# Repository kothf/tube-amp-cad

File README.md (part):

# Tube Amp CAD

Design and simulate vacuum-tube amplifiers in the browser. You draw a
schematic, and a circuit simulator computes the operating points and
waveforms. A curve tracer, an oscilloscope, a spectrum analyzer and a Bode plotter show
the result as bench instruments would.

**Live:** [kothf.github.io/tube-amp-cad](https://kothf.github.io/tube-amp-cad/) ·
also on [aerocat.tech/tools](https://aerocat.tech/tools/)

There's nothing to install, no account and no server. Everything runs on
your machine, and the browser saves your circuit.

**Browsers:** tested in Chrome, Edge and other Chromium browsers (Brave,
Vivaldi, Opera) and in Safari (the whole test suite also runs in WebKit).
Firefox is not tested.

## Contents

- [The schematic editor](#the-schematic-editor)
- [Parts](#parts)
- [Measuring on the schematic](#measuring-on-the-schematic)
- [Drawings, documents and exports](#drawings-documents-and-exports)
- [Instruments](#instruments)
- [Board Design](#board-design)
- [Keyboard shortcuts](#keyboard-shortcuts)
- [How the simulator works](#how-the-simulator-works)
- [Accuracy](#accuracy)
- [Run it locally](#run-it-locally) · [Development](#development) · [Contributing](#contributing)

## The schematic editor

- **Placing parts.** Pick a part in the palette on the left and click the
  sheet; Shift-click places several. The search box at the top of the palette
  finds:
  - parts by name;
  - part numbers: 2N3904, IRF540, 1N4742A, 125ESE, 373BX …;
  - tubes: EL84, 6N2P, 300B …;
  - values: `47k` offers a 47 kΩ resistor or potentiometer, `100n` a
    100 nF capacitor, `47u` an electrolytic, `5H` a choke, `300V` a supply.

  ↓ / ↑ walk the results and Enter picks the marked one (or the first). Each
  row shows a small picture of the part's own symbol; pointing at a part shows
  it large in the preview card under the list, with what it is. Drag a part
  onto the sheet to place it there. Right-click a part (or ☆ in the preview)
  to keep it in Favorites; Recent lists the last parts picked. Click a group's
  title to fold it; the browser remembers which groups are open.
- **Wiring.** Click a pin, click the corners, and finish on a pin or a wire.
  <kbd>W</kbd> starts a wire anywhere. A wire ending on another wire joins it
  with a junction dot; plain crossings stay unconnected.
- **Editing.**
  - Drag parts and their wires follow; drag a wire segment sideways to move
    it.
  - <kbd>Space</kbd> rotates (also while placing or dragging a part; <kbd>R</kbd>
    works too), <kbd>M</kbd> mirrors left to right, <kbd>D</kbd>
    duplicates, <kbd>Del</kbd> deletes, with undo and redo.
  - Mirror works for every part that can rotate, including any part added to
    the library later. So a complementary pair, or a tube taking its grid from
    the right, can be drawn without crossing wires. The oscilloscope mirrors
    too, so its inputs can come in from the right; its screen stays upright.
- **Inspector (right).** Every value of the selected part: resistance
  ("4.7k"), tube type, transformer model and tap, generator level in Vpk, Vrms
  or dBV. With a simulation result it adds:
  - the part's operating point: Va, Vg, Ia, Pa and gain for a tube; Vce, Ic,
    hFE and dissipation for a transistor;
  - checks against the part's ratings.

  With nothing selected it shows a power summary instead: output into the
  speakers, and tube, transistor and resistor dissipation.
- **Live or on demand.** The circuit re-simulates after every edit, or turn
  *Live* off and press *▶ Simulate* (<kbd>Ctrl</kbd>+<kbd>Enter</kbd>).
  - Either way, slow power supplies are run until they have fully settled.
  - The button shows the run's progress ("■ Stop · 48 %"); press it again to
    stop a long run.
  - When a steady-state run and the oscilloscope's power-on transient run at
    once, the status line shows both on one line with one progress bar.
- **Checks.** Unconnected pins, shorted parts, a missing ground, sheet
  connectors without a partner, and parts beyond their ratings: resistor
  power, output-transformer DC current, transistor Vce and dissipation, zener
  power, and for tubes:
  - anode dissipation (Pa) and screen dissipation (Pg2), averaged over the
    signal cycle; screen voltage; cathode current;
  - heater-to-cathode voltage at its worst instant, against the rating for
    that direction (a rectifier's or a raised cathode's "heater negative"
    rating is often higher). The heater is taken as grounded; set *Heater DC
    potential* on the tube for an elevated heater supply;
  - the grid circuit resistance (grid stopper, grid leak, volume pot) against
    the largest the tube allows with cathode or with fixed bias, where too
    much lets the tube run away as it warms;
  - a rectifier's rectified current and peak inverse voltage.

  The tube's inspector shows each of them as a share of its rating. Ratings
  come from Katsnelson & Larionov for the Soviet tubes and from the makers'
  datasheets for the others (RCA, Philips, Mullard, Western Electric); a
  rating a datasheet does not give is not checked.
- **Window tabs at the bottom.** Like the part / assembly / drawing tabs of a mechanical CAD, a strip under the status bar switches between the schematic, the board, the open instruments and the manual inside one browser tab. Schematic and Board are always there; an instrument or the manual gets a tab when opened (or from **+**). × closes a tab, ⧉ moves it to a window of its own for a second monitor (the tab stays dimmed and brings that window up), and a reload keeps the tabs. *View ▾ → Windows as tabs* (on by default) turns them off: every tool in a window of its own, as before.
- **Toolbar.** One row: the *Schematic | Board* switch (the same switch in the Board window leads back; Alt+B and Alt+S from any window; the board is a tab at the bottom of the CAD window), *File ▾*, *View ▾* (the Voltages, Currents and Legend on the schematic (the legend fades while the pointer is over it, so the drawing under it shows), the bill of materials and Checks tabs under it, ticked on or off, Windows as tabs and the interface language), *Edit ▾* (undo, redo, rotate, mirror, duplicate, delete, copy, paste, select all, reusable blocks, renumber), undo / redo, the *Select | Wire | Probe* tool, zoom and *Fit* (wheel zoom and panning stay smooth on big circuits with the stickers and the animation on: the picture is stretched while the wheel turns and drawn sharp when it stops, and only what is on screen is drawn), *● Live | ▶ Simulate | ∿ Animate*, *Analyze ▾* next to Simulate (the instruments: oscilloscope, spectrum analyzer, Bode plotter and curve tracer, each in a tab at the bottom; the analyses: tolerance runs, power sweep, listen, parameter sweep and noise and hum, each a tab under the schematic), and **?**, the Help menu (quick help and shortcuts, F1; the manual; about). The menus follow other simulators: instruments and analyses sit with simulation (Multisim's and LTspice's Simulate menu), the board is reached by its switch (KiCad's Switch to PCB editor, Proteus's tabs) and the manual is under Help, so there is no Windows menu. *RU / EN* switches the interface between Russian and English (also *View ▾ → Interface*): the CAD, the Board window, the instruments and the hover hints follow, every open window at once, and so does the manual (`help-ru.html`, its Russian translation). The right mouse button on a part or wire opens the editing commands there. At 900 px and below the inspector is a drawer that slides in when something is selected (*Inspector* button).
- **Hints and manual.** Every field, readout, instrument setting and model coefficient explains itself when you rest the pointer on it (labels with a dotted underline). The manual, `help.html` (in Russian `help-ru.html`, chosen by the interface language; the *RU / EN* button at the top of its contents switches it), opens from **?** → *Manual* (the Help menu), the help dialog, or **?** in each instrument. It covers:
  - a quick start, then every part and field;
  - all 99 tubes in a sortable table;
  - every readout and the checks;
  - the instruments and the board layout;
  - a design cookbook, and the simulator's equations and limits.

  It is searchable.
- **AI assistant** (AI ▾ and the AI tab under the schematic), with your own
  key for Claude, ChatGPT or Gemini, kept in the browser and sent only to
  that provider:
  - ask about the circuit or the app; the model sees the parts, nets,
    simulated voltages, operating points and Checks, and the manual;
  - *Design from a description*: the model designs the circuit, the CAD
    draws and simulates it and sends the Checks back for revisions;
  - *Tube from a datasheet*: a PDF read into ratings, pinout and a Koren
    model fitted to its plate curves, reviewed before it joins the library;
  - *Explain my circuit*, stage by stage;
  - *Fix the checks*: value changes checked against the parts, applied with
    one click, re-simulated and compared.
- **Auto-tune** (the Tune tab, no key needed): set goals such as "10 W at
  ≤ 1 % THD" and the values that may change; an optimizer tries values, the
  simulator judges each, and the best are rounded to E24/E12. *AI start*
  lets the model pick the values and ranges. With no goals yet, one button
  adds the usual pair: the speaker's power a quarter above what it gives now,
  at ≤ 1 % THD.
- **Layout.**
  - Drag the edge of the palette, the inspector or the BOM to resize it, and
    double-click the edge to reset it. The same goes for the side panels of
    the instrument windows.
  - <kbd>F1</kbd> or the **?** button opens the help with every shortcut and a link to the manual.
  - Shortcuts go by the key's position, so they work with a Russian or any
    other keyboard layout.
- **Reusable blocks** (Edit ▾ → Blocks…): select a stage or a whole
  channel and make it a block, then place it as many times as needed (the
  two channels of a stereo amplifier). A value changed on any copy changes
  on every copy; after changing the drawing of one copy, *Update block from
  selection* redraws the others. Sheet-connector names stay each copy's
  own, designators are numbered per copy, and blocks can be kept in a
  library in the browser for other circuits.
- **Files.**
  - File → Open / Save / Save as (JSON). In Chrome and Edge, Save writes back
    to the opened file after asking; in Safari and other browsers it
    downloads the file.
  - The circuit is also autosaved in the browser, and File → Autosaves…
    keeps a copy every 5 minutes of editing and when the tab closes (the
    newest 60, in this browser only); Open puts one back on the sheet.
  - File → Recent files lists the last 8 circuits opened or saved (and the
    examples opened), newest first; a click opens one again. Chrome and Edge
    read the file itself again; when it is gone, not allowed, or the browser
    cannot open files by itself, the copy kept in the browser at the last open
    or save opens instead (the status line says so). *Clear recent files*
    empties the list.
  - File → Revisions… keeps a project's history as numbered revisions (r1,
    r2…) with a message, what changed, pictures of the sheet and the board,
    milestones, Compare on the sheet and Restore. *Kept in* chooses where: on
    aerocat.tech (the site's owner only, `server/share/`), or in a **vault**,
    a folder on your computer that you choose (`cad-vault.js`; Chrome and
    Edge read and write it, Safari and Firefox open it read only). A vault holds plain files: a folder for each project with
    `project.json`, and each revision as `r<n>.json` (File → Open reads it)
    with its pictures and release files. Add as many vault folders as you
    like, one for each project for example, and switch between them in
    *Kept in*; nothing leaves the computer. The project manager
    (`projects.html`) lists either store and copies a project with all its
    revisions between the folder and the site.
  - File → Share link… packs the whole design (circuit, imported tubes,
    board) into a link; whoever opens it gets the same circuit. On
    aerocat.tech the link is short (`/s/<id>`, kept by the link store in
    `server/share/`); elsewhere the design rides after `#` in the address.
  - Icons: the tools, Fit and Inspector, and every item of the File, View,
    Edit, AI and Windows menus (in Board Design the Route, Board, Export and
    View menus too) carry a line icon from the app's own set (`icons.js`,
    drawn in the text colour, nothing loaded from elsewhere). The names stay
    next to them; a narrower window shows the toolbar buttons by their icon
    alone, the tooltip naming each, so the toolbar keeps one row.
  - The open file's name shows in the toolbar and the browser tab's title; a
    yellow • marks unsaved changes (the board's too). A circuit not saved to
    a file yet (a new one, or an example) shows its title block's title (or
    its identification number) in grey italics, such as "NE555 metronome:
    astable into a speaker"; "Untitled" only when the title block is empty.

## Parts

| Group | Parts |
|---|---|
| Passive | resistor (with power rating, marked in the symbol per ГОСТ 2.728), potentiometer (lin/log), capacitor, electrolytic, choke with DCR, speaker: an ideal resistor, or a **loudspeaker** from its Thiele–Small parameters (Re, Le, fs, Qms, Qes; typical guitar and hi-fi drivers to start from) with its impedance and phase curve in the inspector; **protection**: fuse (5 × 20, 6.3 × 32, TR5; Checks from 75 % of its rating), inrush limiter NTC (Ametherm SL series, simulated at its self-heated resistance), varistor (TDK SIOV); capacitors take a voltage rating that Checks watches; **headphone loads** 32, 250, 300 and 600 Ω with their resonance peaks; **potentiometer** tapers lin / log / reverse log, sections R1.1 + R1.2 as one dual-gang (stereo) pot, an optional on–off switch (switched pot) |
| Switches & relays | changeover switch, on–off toggle, push buttons (normally open / closed), rotary selector (2–12 ways), all ganged by section names; **relays** Omron G5LE-1 (SPDT) and G5V-2 (DPDT) with 5 / 12 / 24 V coils (coil resistance and inductance, must-operate and release, timing checked against ngspice); **vactrols** VTL5C3 and VTL5C1 (the cell following the LED's current, with the datasheet's turn-on and turn-off times) |
| Transformers | generic single-ended and push-pull/UL output transformers with a **Model** list of Hammond and Edcor parts (the part remembers its model and shows it, marked *(edited)* when you type your own values over it), a saturating core and a **Core material** whose hysteresis loop gives the bass distortion and core loss of a real transformer (silicon steel, nickel or amorphous), and a generic power transformer; **interstage and input transformers** (turns ratio, optional centre-tapped secondary, primary and leakage inductance, winding capacitance, DCRs, the DC the core is gapped for; typical interstage, microphone, moving-coil and line presets), checked against ngspice's coupled inductors; the seven **Hammond 125SE** output transformers and 25 **Hammond 300-series** power transformers, modelled from the maker's drawings (winding resistances, inductance, excitation, no-load voltages, ratings) |
| Tubes | every tube's anode temperature from its dissipation, glowing red when over-driven (red-plating); **110 tubes**: the Soviet receiving tubes from Katsnelson & Larionov, «Отечественные приёмно-усилительные лампы и их зарубежные аналоги» (1981), including triodes and double triodes (6С2С, 6С33С, 6Н1П…6Н33Б), voltage and output pentodes (6Ж1П, 6Ж32П, 6П1П, 6П3С, 6П14П, 6П27С…), triode-pentodes as two sections (6Ф1П, 6Ф3П, 6Ф4П, 6Ф5П) and kenotrons (5Ц3С, 5Ц4С, 6Ц4П…), with the handbook's ratings and pinouts; plus Western tubes from their makers' datasheets (12AX7, 12BH7A, 6CG7, EL84, 6AQ5A, ECL82, EL34, KT66, KT88, 6AS7G, 300B, 211, 845, GZ34, 5Y3GT, EZ81, 6X4…). Pentodes can be used triode-connected. **Import SPICE model…** adds any tube model of your own (see below).; **mercury-vapour rectifiers** 83 (full-wave) and 866A (half-wave): a constant 15 V arc drop, glowing blue under Animate; heaters glow and warm up from switch-on under Animate |
| Semiconductors | **diodes**: standard rectifiers 1N4001/1N4004/1N4007, 1N5404/1N5408, fast and ultrafast UF4007, UF5408, MUR160, MUR460, HER108, FR107, Schottky BAT85, 1N5817, 1N5819, 1N5822, SB1100, SiC Schottky C3D02060A, C3D04060A, C4D02120A, the 1N4148, with reverse recovery; **bridge rectifiers** DF04M, DF10M, W04G, W10G, B250C2300-1500A, GBU4J, GBU8K, KBU8K, KBPC2510, KBPC3510; zener diodes, the 1 W 1N4728A … 1N4764A series and 5 W 1N5349B … 1N5388B (3.3–200 V); LEDs (red, yellow, green, blue) for cathode bias; **NPN** 2N2222A, 2N3904, BC107, BC547B, BD139, MPSA42, MJE340 and **PNP** 2N2907A, 2N3906, BC177, BC557B, BD140, MPSA92, MJE350; **drivers and power output** in complementary pairs: 2SD669A/2SB649A, 2SC4793/2SA1837, MJE15032/MJE15033, TIP41C/TIP42C, 2SC5200/2SA1943, MJL3281A/MJL1302A, MJL21194/MJL21193, and in TO-3 (on wires, for a chassis heatsink) MJ15003/MJ15004, MJ15024/MJ15025, 2N3055/MJ2955; **germanium** (VBE about 0.2 V, low fT): USSR MP39B, MP40A, MP41A, MP42B, MP25B, MP26B, MP38A (NPN), GT402G/GT404G, P213B (МП39Б … П213Б) and Western AC127/AC128, AC187/AC188, OC71, NKT275, 2N404, AD149, AD161/AD162, with their collector leakage (ICBO, doubling every 10 °C); every bipolar transistor has a **Temperature** (VBE −2 mV/°C, hFE and leakage rising) and **Cooling**: self-heating in free air or on one of four shared heatsinks, the junction at the temperature its own dissipation gives (class-AB bias drift, thermal runaway, a VBE multiplier tracking its outputs on the heatsink); a SPICE part's transistors follow its Temperature by their own XTI, EG, XTB and TNOM, and a lone transistor model can heat itself too; **N-MOSFETs** 2N7000, BS170, IRF510, IRF540, IRF820, IRF840, IRFP240, IRFP250, IRFP460, the laterals 2SK1058 and ECX10N20, and the depletion DN2540 and LND150 for current sources; **P-MOSFETs** BS250, IRF9540, IRF9610, IRF9640, IRFP9240 and the laterals 2SJ162 and ECX10P20. The power models are fitted to the datasheets (hFE and its fall at high current, VBE, capacitances; for MOSFETs the typical transfer curve); the drivers and power parts (and BD139/BD140) also have base and emitter resistance fitted to the datasheet's typical VBE curve, so their VBE rises with the current as on the bench; **JFETs** (SPICE JFET, checked against ngspice): N-channel J201, J113, J310, 2N5457, MPF102, 2SK170, LSK170B, 2SK30A, P-channel J175, 2N5460, 2SJ74 |
| Sources | DC supplies: DC supply (positive for B+, negative for grid bias, with an internal resistance), power rail (the one-pin VCC arrow: an ideal supply to ground, joined by name), current source (constant current with an output resistance). AC sources: signal generator (sine, square, triangle; Vpk, Vrms or dBV; and for the Transient tab pulse, piecewise linear, exponential and FM, with SPICE's PULSE, PWL, EXP and SFFM parameters), AC mains (feeds a power transformer). Instruments and records: **guitar pickup** (EMF behind the coil's R and L, its capacitance and the cable; single-coil, P-90 and humbucker presets) and **phono cartridge** (moving magnet or moving coil, playing a tone cut with the RIAA curve, or flat). Controlled sources: voltage-controlled voltage (SPICE E) and current (SPICE G) sources, for behavioural models (a G with ra in parallel is a tube's small-signal model); **batteries**: 9 V PP3, AA cells and packs, Li-ion 18650 and packs, 12 V lead-acid, with the charge left and the internal resistance |
| Gas-discharge tubes | **voltage regulators** 0A2, 0B2 (miniature), 0A3, 0C3, 0D3 (octal): dark until the striking voltage, then the maintaining voltage plus the regulation over the current range, out below the extinction current (so 0.1 µF across one makes a relaxation oscillator); Checks for not striking and the current range; **neon lamps** NE-2, NE-2H, ИН-3 (strike, maintain, either polarity; flashers); **magic eyes** 6E5, 6Е5С, 6U5 (triode fitted to RCA's data, the shadow from the ray-control voltage). Under Animate the neons glow orange, the regulators violet and the eyes open and close; **magic eyes** EM84 / 6Е3П (bars) and 6Е1П (noval fan) from their datasheets; **incandescent lamps** #47, #44, #1869, #327, 60 W 230 V (tungsten resistance by current, glowing on the sheet); **nixie** ИН-14 (the lit digit glows) |
| Ground & connectors | Ground, sheet connector; **jacks** (6.35 mm mono switched, mono, stereo, 3.5 mm stereo, RCA), **IEC C14 inlet**, **terminal blocks** (2–8 ways, 5.08 / 7.5 mm), **pin headers** (2.54 mm), **Faston tabs** (6.3 / 4.8 mm), **XT power connectors** (Amass XT30 / XT60 / XT90, male and female, right-angle or vertical PCB, solder cups, on a lead, XT90-S anti-spark; Amass order codes in the BOM; detailed 3D / STEP bodies with shroud, pins and sockets), with the makers' footprints |
| Integrated circuits | **op-amps**: TL071, TL072 (dual), TL074 (quad) with JFET inputs, LM741, LM301A (compensated by your own capacitor between pins 1 and 8), LM324 (quad, single supply, inputs and output down to V−) and the audio types NE5532 (dual, low noise), OPA134 / OPA2134 (FET input) and LM4562 (55 MHz); each with its datasheet's open-loop gain, gain-bandwidth, slew rate, output swing, short-circuit current, input bias and supply current. The amplifiers of a dual or quad (DA1.1 … DA1.4) share one DIP-8 or DIP-14 on the board; **NE555 timer** (DIP-8 on the board): the 5k–5k–5k divider, both comparators, the latch, reset, the output (VCC − 1.4 V high, 8 Ω low, about 120–250 mA at most) and discharge stages and the chip's supply current, from TI's data. Its latch switches at the instant a comparator crosses, not on the time grid, so the timing does not depend on the step; the inspector reads the output's frequency and duty cycle; **voltage regulators**: LM317, LM317L, LM338, LM337 (adjustable) and 7805, 7809, 7812, 7815, 7824, 78L05, 78L12, 7905, 7912, 7915 (fixed), with the reference, error amplifier, current limit, dropout, line regulation (ripple rejection) and an LM317's minimum load; **TL431** shunt reference; **power amplifiers** LM386 (internal gain network, 20–200), TDA2050 and LM3886 (with its mute current), their output power at clipping as the datasheets |
| Instruments | two-channel oscilloscope (its screen live on the schematic, full window on double-click), with the spectrum analyzer and the Bode plotter reading its channels; **panel meters**: moving-coil ammeter or voltmeter and a VU meter, the needle on the sheet with a meter's ballistics under Animate |
| Document | IEC 61082 drawing frame with title block, text note |

### Your own tube models (SPICE import)

*Import SPICE model…* in a tube's inspector adds a tube from any SPICE model:
Norman Koren's, Ayumi's, Duncan's, Derk Reefman's or a maker's library.
Paste the `.SUBCKT … .ENDS` text or open the file.

- **It runs as written.** Behavioural sources (`B`, `E`/`G VALUE={…}`, linear
  `E`/`G`) and their expressions are evaluated directly, with `.PARAM`,
  `.FUNC`, `PARAMS:`, continuation lines, unit suffixes and the usual
  functions (`exp`, `ln`, `pwr`, `pwrs`, `uramp`, `limit`, `if`, `atan`, `tanh`
  …). Internal nodes are solved too, such as the grid-current resistor and
  diode of Koren's models. Capacitors are left out, since the simulator's
  tubes have none.
- **Pins:** read from the model's comment (`; P G K`, `A G2 G1 K` …). Without
  a comment, the assignment that behaves like a tube is chosen. You can always
  change it, and the curves show at once whether it is right.
- **What it's like:** each imported tube takes its socket, pinout and heater
  from a tube you choose, so the board footprint and the warnings work. Pa
  and Va maximums are set in the dialog.
- **Parts already placed:** a placed part keeps its own copy. When its
  library part has changed, the library dialog (*Update them*) and the
  part's inspector (*Update from the library*) bring it up to date; values,
  part numbers and wires stay, one Undo takes it back.
- **Where it's kept:** in the browser, and inside every circuit file that
  uses it, so the file opens on another computer. The curve tracer shows it
  with its model, and the SPICE netlist export writes the subcircuit as
  imported.
- **Checked:** Koren's published 12AX7 model gives the same currents as the
  built-in Koren equations with the same parameters.

### Any part from a maker's SPICE model (the SPICE part)

A part the library does not have (another op-amp, a regulator, a power
MOSFET, a transistor, a diode) runs on the model its maker publishes. Place
*SPICE part* (Integrated circuits), press *Model…* in its inspector and paste
the model or open the file.

- **One simulator.** The model is turned into the simulator's own elements,
  so the part runs with the valves in everything the program does: live
  simulation, steady state, tolerance runs, Tune, the instruments.
- **What it reads:** `.SUBCKT … .ENDS` (nested subcircuits, `PARAMS:`,
  `.PARAM`, `.FUNC`) or a lone `.MODEL`; R, C, L, coupled inductors (`K`), DC
  sources, diodes (series resistance, breakdown), bipolar transistors
  (Gummel-Poon with leakage terms and terminal resistances), MOSFETs (levels
  1, 2 and 3 each by its own equations with the bulk as a fourth pin, bulk
  junctions and Meyer's gate capacitances; LTspice's `VDMOS`), JFETs, controlled sources
  `E G F H` (linear, `VALUE={…}`, `TABLE`, `POLY`), behavioural `B` sources
  with `V()` and `I()`, switches `S` and `W`; PSpice, LTspice and ngspice
  spellings.
- **Symbol and pins:** a lone transistor or diode model takes that device's
  symbol; five pins are offered as an op-amp in the usual order; anything
  else is a box with the model's pins. Each pin of the model is set to a pin
  of the symbol, to ground or to nothing.
- **Transfer functions:** `LAPLACE` sources (PSpice's and LTspice's
  spellings), any ratio of polynomials in s, run exactly; `FREQ` tables
  fitted by a ratio of polynomials (vector fitting).
- **Transmission lines:** lossless `T` lines (`Z0=` with `TD=`, or `F=` and
  `NL=`, or PSpice's `L`, `C` and `LEN`), delayed exactly in the waveform and
  as e^(−jωTD) in the frequency response.
- **What it refuses, with the reason:** `LAPLACE` other than a ratio of
  polynomials, a `FREQ` table's `DELAY`, `CHEBYSHEV` filters,
  lossy transmission lines, digital (`A`) devices, BSIM MOSFETs, expressions of
  time. Junction capacitances follow the voltage across them and step their
  charge; a transistor's transit times (TF, TR) shape the waveform and the
  frequency response; a VDMOS power MOSFET's gate-drain capacitance follows
  CGDMIN … CGDMAX with its drain voltage (the Miller plateau).
- **Where it's kept:** inside the circuit file. The SPICE export writes the
  part as one line with its model as it came; the board gives it a DIP-8 /
  SOIC-8, a transistor or diode case, or a DIP in the model's pin order.
- **Checked:** a bench of device models, sources, a switch, a table and a
  polynomial gives ngspice's operating point within 0.1 %
  and its frequency response to 10 MHz within 0.02 dB
  (`tests/spicenet.test.mjs`), and `npm run test:ngspice` runs 64 makers'
  op-amp models against ngspice (`tests/models.mjs`): the output voltage
  within 2 %, gain and phase from 10 Hz to 1 MHz within 0.1 dB and 1° up to
  20 kHz, 0.3 dB and 3° up to 1 MHz.

### Pin rules (ERC)

Every pin has a role (an input, an output, a supply pin, a source, a plain
terminal) and the Checks hold the wiring to it (`cad-erc.js`):

- an input with **no DC path**: a grid behind its coupling capacitor without
  a leak, a gate, a base or an op-amp input with nothing but capacitors on
  it (the path is followed through resistors, chokes, windings, switches);
- an IC's **supply pin fed by nothing**, or both supply pins on one net;
- **outputs wired together**, to ground or straight to a supply;
- a supply shorted by its own wiring.

A SPICE part takes the roles of its symbol. All 20 examples pass.

### Your own parts library

*My library* at the top of the parts panel holds your own parts: each is data,
not code, a drawing with pins, a footprint and, if you give it one, a SPICE
model. *Parts library…* in the panel opens it.

- **Add part… by part number:** type the maker's part number (TL072CP, 2N3904,
  IRF540N), choose the package, place it. The SPICE model is looked up in the
  public [KiCad-Spice-Library](https://github.com/kicad-spice-library/KiCad-Spice-Library)
  (an index of about 49,000 names ships with the app, `spice-index.json`; the
  one model's file is downloaded when you add the part). The drawing follows
  from what the model is; a dual or quad op-amp becomes a library part with a
  unit per amplifier. A number the app has built in (2N3904, TL072, LM317T,
  NE555P) is offered as the built-in part first. No model for the number: the dialog says so and takes
  the maker's file from you instead.

- **From KiCad's libraries:** *Add from KiCad files…* reads symbol libraries
  (`.kicad_sym`) and footprints (`.kicad_mod`), several at once. A symbol
  library lists its symbols with a Find box; tick the ones to add. Derived
  symbols (`extends`) come with their parent's drawing.
- **Drawn here:** *New part…* and *Edit drawing…* open the symbol editor:
  Line, Rectangle, Circle, Text and Pin tools, Select to move and delete,
  Undo, units of a package, a table of the pins, and *Make a box from a list
  of pins* (one line per pin, as on a DIP or with sides) for ICs. Pins snap
  to the sheet's grid; a pin number used twice is refused.
- **Footprint:** a part takes the footprint its symbol names or its KiCad
  filters allow as soon as that footprint is in the library; the list shows
  the ones with a pad for every pin first. A pin goes to the pad of its
  number.
- **Footprint drawn here:** *Draw…* and *Edit…* beside the Footprint list open
  the footprint editor, in millimetres: *Make a usual package* (DIP, a row,
  SOIC, QFP or two pads from the count, pitch, row distance, pad and hole),
  Pad, Hole, Line, Rectangle and Circle tools, a grid from 2.54 to 0.1 mm,
  typed coordinates, a table of the pads, Undo, zoom. A pin left without a
  pad is named; every part that uses the footprint follows an edit.
- **SPICE model:** *Model…* sets a maker's `.SUBCKT` or `.MODEL` on the
  part's own pins; the part is then simulated as written (see the SPICE part
  above). Without a model it is left out of the simulation.
- **Units:** a dual op-amp's amplifiers and supply pins are placed unit by
  unit (the inspector's *Unit of the package*) and share one footprint under
  one designator (DA1.1, DA1.2, DA1.3). They are simulated: a model of one
  amplifier set on unit A goes on every unit drawn like it, with the supply
  pins of the package shared; a model of the whole package is used once.
- **Where it's kept:** in this browser (IndexedDB), and as a file
  (`my-parts.tubelib`) with *Save as a file* / *Open a library file…*. A part
  on the sheet carries its drawing, footprint and model in the circuit file,
  so the circuit opens anywhere.
- **Code:** `part-lib.js` (data, no DOM), `cad-symedit.js` (the symbol
  editor), `cad-fpedit.js` (the footprint editor), `cad-library.js` (the dialog and
  the store), `LIB.part` in `cad-components.js`, `KicadImport.readSymbols` /
  `readFootprint`; tests in `tests/partlib.test.mjs` and
  `tests/e2e/08c-parts-library.mjs`.

### Examples

**File ▾ → Gallery…** opens circuits drawn from published sources and compared
with them (see [Accuracy](#accuracy)), and five transistor power amplifiers of
the app's own (7 to 12 transistors each) on SMD boards. The **start screen** (shown when the CAD
opens on an empty sheet, and from *File ▾ → Gallery…*) has *New circuit*,
*Open file* and every example as a picture of its first sheet, by kind; untick
*Show this when the CAD opens* to start straight on the sheet. The pictures are
drawn by `node scripts/example-thumbs.mjs` (run it after changing an example).

The example schematics are drawn to be read: signal from left to right,
supplies at the top and the bottom, one ground bar with a single ground symbol
per area instead of a symbol at every part, each supply rail as one bus with a
single rail symbol, the transistor amplifiers' supply terminal with its
decoupling capacitors in one block, square corners, and no wire through a part
or a label.

Every example also carries a finished two-layer board, laid out the way a
board designer would place it rather than by the automatic placer: signal
flowing from the input jack across to the output transformer leads, the input
kept away from the output and the supply, grid parts and grid leaks at their
socket pins, cathode parts under their valve, anode loads beside it, heaters
hand-routed as a pair (one wire on each layer, side by side) along an edge or a
corridor between the valves, B+ along the edge, hot resistors kept 10 mm or more
from electrolytics, power devices on the heatsink edge, panel parts (jacks, pots,
terminals) on the board edges, M3 screw holes in the corners and within 40 mm
of every valve socket, and a ground pour on the bottom. The grid router routed
the rest; every board opens with 0 connections open and 0 rule messages:

| Example | Parts | Source |
|---|---|---|
| Gubin three-tube amplifier | tubes | Igor Gubin, radionic.ru: stereo single-ended 6N23P-EV + 2 × 6P14P, no coupling capacitors, pentode / triode switch |
| Gubin stereo amplifier with 5Ц4С supply | tubes | GUB-245-01 (Radio 4/1957; musicangel.ru Fig. 3), three sheets: 373BX transformer, 5Ц4С, capacitor input and 2.5 H choke; two 6N23P-EV + 6P14P channels; with a routed two-layer board (no rule violations) |
| Single-ended 2A3, Hammond 1627SEA | tubes | RCA 2A3 data (250 V, −45 V, 60 mA, 2.5 kΩ, 3.5 W): 6SN7 driver, cathode bias; 3.6 W at 1.8 % THD |
| Push-pull EL84 ultralinear, Hammond 1608 | tubes | Mullard-style: 12AX7 stage, split-load phase splitter, 2 × EL84 UL into 8 kΩ, 14 dB feedback; 11 W at 0.9 % THD, the core saturating at 15 Hz |
| Push-pull 6V6 guitar amplifier, Hammond 1750H | tubes | Tweed-style: 12AX7 stage, split-load splitter, cathode-biased 6V6GT pair, no feedback; 7.7 W at 2 % THD |
| 12AX7: plate resistor vs current source | tube + transistor | J. Broskie, TubeCAD (2000): gain 70 with a 150k plate resistor, 100 with an MPSA92 current source |
| 12AX7 stage + IRF820 follower | tube + MOSFET | The GE 12AX7 data sheet's resistance-coupled stage (gain 50) driving a MOSFET follower, which feeds an 8 Ω speaker through a parafeed output transformer (about 0.5 W) |
| 10 W complementary MOSFET amplifier | MOSFETs | homemade-circuits.com, fig. 1 |
| 2N3904 common emitter, RE unbypassed | transistor | University of Washington lab notes (2017), bench measurements |
| 2N3904 common emitter, RE bypassed | transistor | the same, with 10 µF across RE |
| 12 W amplifier, complementary feedback pairs (SMD) | transistor | this app's own design: ±15 V, current-source input and VAS, CFP outputs in D²PAK; 12 W at 1 % THD; all-SMD board |
| 50 W amplifier, MJL4281A / MJL4302A outputs | transistor | this app's own design: ±30 V, LED-referenced current sinks, CFP outputs in TO-264 on the board edge; 51 W at 1 % THD |
| 14 W class-A amplifier, current-sink output | transistor | this app's own design: ±18 V single-ended class A, 4 × TIP36C, 1.8 A sink; 14 W at 1 % THD |
| 30 W quasi-complementary amplifier (SMD) | transistor | this app's own design: ±25 V, current mirror, bootstrapped VAS, TIP41C outputs in D²PAK; 32 W at 1 % THD; all-SMD board |
| 40 W amplifier, complementary MOSFET output (SMD) | MOSFETs | this app's own design: ±30 V, IRF540N / IRF9540N in D²PAK; 38 W at 1 % THD; all-SMD board |
| NE555 astable multivibrator | 555 | 555-timer-circuits.com: 1k / 10k / 100 nF, 678 Hz at 51.8 % (formula 686 Hz, 52.4 %) |
| NE555 flashing LED | 555 | 555-timer-circuits.com: 1K / 470K / 1 µF, 1.51 Hz (formula 1.53 Hz) |
| NE555 metronome | 555 | 555-timer-circuits.com: 250K speed pot at 50k, 22 µF, speaker; 0.641 Hz (formula 0.648 Hz) |
| NE555 car tachometer | 555 | 555-timer-circuits.com: one-shot 47k / 100 nF, 5.16 ms pulses (1.1 RC = 5.17 ms); meter current proportional to the spark rate |
| NE555 simplest oscillator | 555 | 555-timer-circuits.com: output to capacitor through 10k, 100 nF: 572 Hz at 60 % (a full-swing output would give 721 Hz at 50 %) |

An example opens unsaved (the toolbar shows its title), so *Save* asks for a
file name. Ctrl+Z brings back
the circuit that was on the sheet.

## Measuring on the schematic

- **Voltage and current on every wire.**
  - Each net carries a sticker with its DC voltage, and each run of wire one
    with its DC current and direction ("↓1.38mA"). In a mains-fed circuit
    both are averaged over the settled window, as a meter reads them.
  - **∿ Animate** plays one signal cycle slowed to 3 s: dots run along each
    wire with its DC or its AC current (from the simulation's terminal
    currents at 120 instants, capacitors' C·dV/dt included), chosen by the
    node's voltage. Where the node's DC voltage is at least its AC rms, violet
    dots flow steadily with the DC current; elsewhere pale dots swing with
    the AC current. Each node's wires turn
    orange as it swings up and blue as it swings down. Tube heaters glow
    once simulated and, from the moment Animate is pressed, warm up from
    cold over each tube's own warm-up time.
  - **Play it live under Animate**: drag a pot's wiper (or turn it with the
    wheel) and click a switch, button, selector or switched jack; the
    circuit is simulated again as you turn, and letting go is one undo step.
  - AC is marked apart from DC: a net with AC on it adds it in cyan as
    "~20.1Vrms" after the yellow DC ("162V ~20.1Vrms"); a net with no DC
    shows the AC alone. Wires carrying the signal (AC at least 1 % of the DC)
    glow cyan, so the signal path stands out from supply and bias nets.
  - Currents come from every part's terminal currents and are passed along
    the wiring, so a junction shows how the current splits. On the 12AX7
    above, 1.02 mA from the plate resistor splits into 1 mA anode and 15 µA
    into the scope probe.
  - The stickers are placed where they cover no text, no symbol and no other
    sticker. If there is no room at all, a sticker is left out.
  - Hovering a wire shows its voltage, AC swing and current in the status
    bar. *View ▾ → Voltages / Currents* turns the stickers on and off.
- **Voltmeter probe.** The *Probe* tool (<kbd>P</kbd>, beside Select and
  Wire) reads a node like a bench meter. Point at any wire or pin after a
  simulation: a card beside the pointer shows the DC voltage, AC rms,
  peak-to-peak and frequency, with a small scope trace of the waveform
  (DC coupled, triggered, auto-ranging), and the node's wires glow yellow.
  - A click leaves the probe on that node. Its card stays on the sheet and
    keeps reading through edits and new simulations, also after you go back
    to Select: handy with *Live* on while you turn a value in the inspector.
  - <kbd>Esc</kbd>, the card's × or a click on empty sheet removes it.
- **Scope screens on the schematic.** An oscilloscope part shows its two
  channels live; double-click it for the full instrument.
- **Power-on transient.** The oscilloscope can show the first seconds after
  switch-on: capacitors start empty and every source switches on at t = 0.
  In every scenario but *Hot restart* the tubes' cathodes start cold as well and heat with
  their own time constant, from the heater's power and the kind of cathode
  (directly heated 1–2 s, standard indirectly heated 5–8 s, heavy power tubes
  8–12 s, slow-start rectifiers such as the GZ34 10–15 s; or the tube's own
  *Warm-up time constant*), emitting by Richardson's law. The run then
  shows B+ overshooting on cold tubes, draws the capacitors' voltage ratings
  as dashed lines, and warns of a capacitor over its rating, a rectifier
  overdrawn while its cathode is still cold (cathode stripping) and a
  switch-on surge. *Auto* duration covers the slowest warm-up (5–60 s).
  A report strip under the screen lists these events in time order, tagged
  Critical, Warning or Info (B+ settling to ±1 % among them); click one to zoom
  there. Time presets (keys 1–4: Inrush, Warm-up, Settled, Whole) and a log
  time axis show the millisecond inrush and the seconds of warm-up alike.
  Warm-up lanes show each tube's emission rising ("warm at" 90 %, orange
  where it was overdrawn cold); any capacitor can be plotted from the run
  without a probe, and B+ is plotted by itself when no probe is wired.
  *Scenario*: cold start, hot restart, a standby switch (B+ after the
  heaters) or a soft start (a resistor or the NTC shorted by a relay). The
  trace draws as the run goes, with the time left; *Stop* keeps the record.

## Drawings, documents and exports

- **IEC drawings.**
  - Symbols follow IEC 60617.
  - Designations use the classic letter codes (R1, C1, L1, T1, VL1.1, VD1,
    VT1, HL1, SA1, BA1, G1, P1, as in ГОСТ 2.710), with automatic
    renumbering in reading order.
  - Tube pin numbers sit beside each terminal; the section follows the
    designation (VL1.1 / VL1.2).
  - Labels are placed per IEC 61082-1: left of vertical symbols, above
    horizontal ones.
- **Sheets.**
  - *File → New* starts a sheet with an ISO 5457 frame, a reference grid and
    an ISO 7200 title block (A4 to A1, landscape or portrait). *File → Add
    sheet* adds further sheets. A title block value too long for its cell
    wraps onto two or three lines instead of running into the next cell.
  - Sheet connectors with the same signal name join their wires across
    sheets and show where their partners are, grouped by row: "A3,5 B2,5,8"
    (on several sheets "1/A3,5 2/C1,4"). A name used five times or more (B+,
    a bias line) reads as a supply rail and shows no list; hovering any
    connector shows all its partners' zones in the status bar.
  - Frames are locked against accidental moves; unlock one in its inspector.
  - A circuit with several sheets opens on sheet 1. The Sheet list, or <kbd>F</kbd>
    pressed twice, shows them all.
  - A scroll bar under the drawing marks every sheet: drag it to scroll, click a
    sheet's mark to show it, or step between sheets with its arrows (Page Up /
    Page Down).
- **PDF and PNG.**
  - *Print…* (Ctrl+P) prints the sheet in view, all sheets or the bill of
    materials through the browser's print dialog; in the Board window it prints
    the copper layers at 1:1, the toner-transfer pages, the assembly drawing or
    the drill map.
  - *Save as PDF* writes every sheet as a vector page.
  - *Export sheet…* saves the sheet in use, each sheet as its own file, or
    all sheets in one PDF.
  - PNG at 150, 300 or 600 dpi, black on white like the PDF or in the
    editor's colours.
- **Bill of materials.** *View ▾ → Bill of materials* (<kbd>B</kbd>) opens the parts list
  under the schematic (its other tab, *Checks*, lists every wiring problem and part beyond its rating):
  - equal parts on one line with designator ranges (R1-R4); both sections of
    a dual tube count once; a tube-socket line per base;
  - ratings (resistor wattage, transistor Vceo / Ic / Ptot / package,
    transformer ratings), and for each capacitor the first standard voltage
    rating at or above 1.25 × the peak voltage the simulation puts across it
    (a series string of 450 V parts above 550 V for an electrolytic);
  - a part made SMD on the board names its package ("Resistor, SMD 1206"),
    on a line apart from the through-hole parts of the same value;
  - the simulated worst case: dissipation, capacitor peak voltage, LED
    current;
  - a part number you can type in, saved with the circuit. A maker's number
    fills the *Package* column. *Look up* asks DigiKey's parts database
    (with your own free DigiKey API key, kept in your browser) for the
    package, case size, height and lead spacing; a few things are read from
    the number itself with nothing fetched (a size written in it, a leaded
    resistor series' body and leads, a chip size, a film capacitor's spacing,
    a semiconductor's package from its order code). Amber where it disagrees
    with the schematic. Board Design
    takes the footprint it names, and the silkscreen and 3D body follow the
    real size (or a size set by hand in the board inspector).

  Click a line to select its parts; selecting a part scrolls to its line.
  Export as TXT, CSV, XLSX or PDF.
- **Tolerance runs.** *Analyze ▾ → Tolerance runs* opens the *Tolerance* tab
  under the schematic. It simulates the circuit as drawn and then once per run
  with every resistor, pot and capacitor at a random value within its
  tolerance (±5 % and ±20 % by default) and every tube drawing more or less
  current than its model (±20 %). The table shows each value's nominal, min,
  mean, max and spread over the runs, and how many runs took a part over its
  rating:
  - each tube's Ia, Va and Pa, each transistor's current and dissipation,
    each speaker's output and each scope channel's AC;
  - values are normally distributed with the tolerance as 2σ, cut off at the
    tolerance; a seed repeats the same runs;
  - the runs share every processor core. On a circuit slow to settle (a
    valve-rectified supply, say) each varied run starts from the circuit as
    drawn already settled, so it has only a short way to go: the stereo
    Gubin example's 10 runs take 5.4 s instead of 11 s on 4 cores, with the
    same table.
- **Power sweep.** *Analyze ▾ → Power sweep* opens the *Power* tab under the
  schematic. It simulates the circuit at a row of input levels (from −24 to
  +12 dB of the generator's level by default; every generator is scaled
  together, the mains is not) and reads the output power at 1 %, 5 % and
  10 % THD:
  - the output is a speaker's power or a scope channel's AC;
  - a chart of THD and the 2nd and 3rd harmonics against the output, and a
    table of every level, with *Use* to set the generator to it;
  - around the THD marks the sweep adds levels where the distortion jumps
    between two of them, so a clipping output stage is read closely. The
    stereo Gubin example reads 1.71 W at 1 % THD in 12 s on 4 cores.
- **Listen.** *Analyze ▾ → Listen* opens the *Listen* tab under the schematic: a
  recording played through the simulated circuit, heard through the
  computer's speakers, with A/B between input and output as it plays:
  - a guitar riff made here, the generator's own tone, or your WAV or MP3 file
    (a stereo file drives two generators, two speakers play in stereo);
  - the level in dB from the generator's amplitude, to push the circuit into
    clipping and hear it;
  - rendered at 48 kHz, every sample a simulation step, a piece of the clip per
    core (each with a 0.4 s lead-in from the settled circuit, joined with a
    crossfade, on whole mains periods); *Save WAV* keeps the output.
- **Parameter sweep.** *Analyze ▾ → Parameter sweep* opens the *Sweep* tab under
  the schematic: one value of one part (a resistor, a capacitor, a pot's
  wiper, a supply's voltage, a generator's frequency…) stepped over a range,
  log or linear, the circuit simulated at every step on all cores:
  - a table of every tube's Ia, Va and Pa, transistor current and
    dissipation, speaker power and THD, scope channel AC and THD, each with a
    trend line, its range and the steps over its rating;
  - click a line to plot it against the value; a scope channel also overlays
    its wave at every step; click a step to set the part to it;
  - it starts on a resistor and plots the speaker's power (or the first scope
    channel), so *Run* gives a useful curve straight away.
- **Transient.** *Analyze ▾ → Transient* opens the *Transient* tab under the
  schematic: the circuit run in time from its own start to its own stop, the
  general-purpose time simulation (SPICE's `.tran`):
  - *Stop* and *Max step* (blank = Stop/500), *From* (when the record
    starts), a start from the operating point or from zero (SPICE's `uic`),
    and initial conditions (`.ic`) as `out=4 C3.1=0`;
  - the steps are adaptive (the error of each step is estimated from the
    last three; linear capacitors and inductors are integrated by the
    trapezoid rule, the rest by Gear), and the corners of every source's
    waveform are hit exactly;
  - traces by net name, connector, scope channel (`P1 CH1`) or part pin
    (`R3.2`); the chart draws min/max per pixel, a cursor reads every trace,
    drag to zoom, double-click to show all; min, max, p-p, average, RMS and
    end value per trace, and *CSV* writes them all;
  - a waveform viewer: any part's current (`I(R3)` into its first pin,
    `I(Q1.C)`) and expressions over the run (`V(OUT,IN)`,
    `V(R1.1,R1.2)*I(R1)` in W, `d()`, `integ()`, `db`, `abs`, `min`/`max`…,
    with units that follow the arithmetic, `wave-math.js`); several panes,
    each with its own scale, in time or as a spectrum (*FFT*, Hann window,
    the strongest line named); cursors A and B (click, Shift+click) with Δt,
    1/Δt and each trace's values, the figures taken between them; *Keep as
    reference* draws a run dashed under the next ones;
  - **DC sweep** (the tab's first list; SPICE's `.dc`): the operating point at
    2 to 1001 values of a part's value (a supply's voltage, a current source,
    a resistor, a pot…) or of the temperature of every transistor (by its own
    XTI, EG, XTB, as SPICE), each point continuing from the one before; the
    same viewer with the swept value on the axis. Checked against ngspice's
    `.dc` on six circuits (diode, zener knee, BJT output curve, BJT bias
    against temperature, MOSFET transfer curve, current-fed diode) within
    0.5 % of the swing, `tests/dcsweep-ngspice.mjs`;
  - **Measurements** (SPICE's `.meas`): *+ Measure…* adds max, min, p-p,
    average, RMS, integral, value and slope at a point, first crossing of a
    level, rise and fall time (10–90 %), overshoot, settling time (2 %),
    period, frequency and duty cycle of a trace, over the span shown or from
    cursor A to B;
  - the signal generator's *pulse*, *PWL*, *exponential* and *FM* waves and
    the `PULSE`/`SIN`/`EXP`/`SFFM`/`PWL` sources and `time` in B sources of a
    SPICE part play here (the other analyses take their DC value).
  - Checked against ngspice's `.tran` on ten benches (RC, RLC ring,
    rectifier, PWL into RL, EXP, SFFM, current pulse, B source reading time,
    a BJT switch, `uic` with `.ic`): within 1 % of each node's swing (2 % for
    the ring and the switch), `tests/transient-ngspice.mjs`; and four
    switching converters (buck 12→5 V, boost 5→12 V, flyback 24→5 V with
    coupled windings, class-D half bridge): start-up within 2 % of the swing,
    output average within 1 % and ripple within 10 %, `tests/smps-ngspice.mjs`.
- **KiCad.** *Export KiCad project* (File menu) writes a ZIP for KiCad 7 or
  later: the schematic (each symbol as drawn here, dual valves as units of
  one symbol, a sheet per drawing frame), the board when its parts are
  placed, the net classes, custom rules for the clearance by voltage, and
  the symbol and footprint libraries. Pins carry their pads' numbers, so
  *Update PCB from Schematic* pairs the two. Checked with KiCad 7.0.11: on
  every example KiCad's netlist of the schematic joins exactly the pads the
  board joins, and its DRC agrees with the Board window's.
- **Open KiCad project.** *File ▾ → Open KiCad project…* opens a KiCad
  schematic and its board as a circuit here: select the project's
  `.kicad_sch` sheets, its `.kicad_pcb` and `.kicad_pro` together, or a ZIP
  of the folder (KiCad 6 and later; a schematic or a board alone opens too).
  - Symbols the program has a part for become that part and simulate:
    passives, diodes, transistors (by their pin names), op-amps, the 555,
    connectors, and valves under any of their names (ECC83 = 12AX7 = 6Н2П).
    Everything else is kept as KiCad draws it, an *Imported part*: wired on
    the sheet and the board, in the BOM, left out of the simulation.
  - Nets are KiCad's: junctions, local, global and hierarchical labels,
    power symbols, hierarchical sheets (a sheet each), buses by name. On 13
    of KiCad's 14 demo projects the nets equal KiCad's own netlist pin for
    pin (`tests/kicad-oracle.mjs`, with kicad-cli); the one that differs
    has wires drawn on top of each other, which the list points out.
  - The board comes with its outline, footprints as the file has them,
    tracks, vias, pours, keep-outs, holes and texts (top and bottom copper);
    its rules are set from the layout.
  - A project this program exported comes back as it was. A list says what
    came over and what to check.
- **Noise and hum.** *Analyze ▾ → Noise and hum* opens the *Noise* tab under
  the schematic: what the amplifier puts out with no signal:
  - thermal, tube (2.5/gm, pentode partition, 1/f), shot and FET channel
    noise carried to the output; flat and A-weighted over 20 Hz – 20 kHz,
    the input noise, a density chart and each part's share;
  - the supply's ripple at the output (every harmonic of the mains, from the
    steady state with the generators quiet, named after its mains source,
    e.g. "From G1 (230 V 50 Hz mains)") and an estimate of AC heater hum
    (one side grounded, centre-tapped or DC);
  - the signal-to-noise ratio in dB(A), noise and hum together, re 1 W.
- **SPICE.** *Export SPICE netlist* writes an LTspice netlist: tubes as
  behavioural sources with the same equations the simulator uses, transistors
  as Q and M elements with their `.model` lines.

## Instruments

| Curve tracer | Oscilloscope |
|---|---|
|  |  |

- **Curve tracer.** Select a tube or a transistor in the schematic to see its
  curves (transistors: IC–VCE, IC–VBE and hFE–IC, or ID–VDS, ID–VGS and gm–ID,
  from the simulator's own BJT, MOSFET and JFET models, germanium too) with:
  - the operating point;
  - the curve at the circuit's bias;
  - the simulated load line: the last whole cycle of the signal, an ellipse
    when the load is reactive, with arrows for the direction;
  - Pa max and 70 % Pa (a transistor's Ptot and its voltage and current ratings);
  - dissipation, swing, gain and THD at the plate.

  It also has the tube library with socket pinouts, the Koren parameters, an
  LTspice `.subckt` export, and a fitter for your own measured curves.
- **Oscilloscope.**
  - Two channels, DC or AC coupled, with 10× (10 MΩ) or 1× (1 MΩ) probes
    that load the circuit like real ones.
  - Auto volts/div with offset; the timebase locks to the measured frequency;
    edge trigger; X-Y mode.
  - Scale labels on every axis: time below, CH1's volts on the left, CH2's on
    the right. They sit on round values and follow zoom and position.
  - Readouts in Vpp, Vrms, dBV and DC, with the CH1/CH2 gain and phase.
  - Channels with no probe wired are greyed out.
  - *Power-on* shows the switch-on transient with an overview strip of the
    whole record (a tick at each event), the cathodes warming up, capacitor
    ratings, time presets 1–4, *Log time* and a clickable power-on report.
- **Spectrum analyzer.**
  - The FFT is computed over a whole number of cycles, so there is no
    windowing error.
  - A harmonic table up to H10 with THD.
  - Other components (hum, intermodulation) in dBc and dBV.
  - Levels in dBc or dBV.
  - A linear or **logarithmic** frequency axis: on the log axis, 50/100 Hz
    ripple and the audio harmonics read in one view.
- **Bode plotter.** The frequency response at a scope part's channels, from
  1 Hz to 1 MHz:
  - gain in dB (re the generator, or re 1 kHz) and phase, for CH1, CH2, or
    the gain between them (CH2 ÷ CH1, one stage of a chain);
  - the gain and phase at 1 kHz, the −3 dB points either side of it, the
    level at 20 Hz and 20 kHz, and any peak above the 1 kHz gain (an output
    transformer's leakage resonance, a feedback loop short of stability);
  - markers A and B, and wheel zoom on the frequency axis;
  - *Loop gain* mode: the gain around a feedback loop broken at a part (the
    feedback resistor is found and offered first), by Middlebrook's double
    injection, with the unity-gain frequency, phase margin and gain margin
    at both the high and the low end, and a verdict (stable, ringing, will
    oscillate, positive feedback).

  It is the small-signal response: the generator chosen drives the circuit,
  linearized at its idle operating point (signal off; a mains-fed supply at
  its averaged steady state). It reruns after every simulation while the
  window is open.
- **Markers.** Click any graph to place markers A and B:
  - time and voltage with ΔT and ΔV on the scope;
  - frequency and level on the analyzer;
  - Vg, dissipation, gm, rp and µ at a point of the plate curves, with the
    load line through two points.
- **Mouse zoom.** On every graph:
  - the wheel zooms at the pointer (time/div on the scope, the frequency axis
    on the analyzer, both axes on the curves);
  - Ctrl+wheel zooms the vertical axis;
  - right-drag or Shift+drag moves the view.

The windows talk to each other in the browser. The CAD broadcasts each result,
and the instruments only listen, so you can arrange them on several monitors.

## Board Design

*Board* at the left of the toolbar (or Alt+B) opens the PCB layout of the circuit; *Schematic* in the Board window goes back. The board takes its
parts and connections from the schematic, and the CAD saves the layout inside
the circuit file, so one file holds both.

- **Footprints**: every part has a through-hole footprint, chosen from its
  values, as valve amplifiers are built:
  - resistors by power rating (10.16 mm lead spacing at ¼ W up to 50.8 mm at
    20 W);
  - capacitors: film boxes by value, ceramic disc / silver mica for the
    small values, axial film;
  - electrolytics: radial by size, snap-in cans (Ø22–35 mm) and axial cans;
  - diodes and zeners from DO-35 to DO-201AD, SiC diodes in TO-220-2, bridge
    rectifiers in DIP-4, round WOB, inline SIL-4, GBU and KBU, 3 and 5 mm LEDs;
  - fuse clips for 5 × 20 and 6.3 × 32 mm cartridges and TR5 fuses, varistor and
    inrush-thermistor discs;
  - connectors: Neutrik 6.35 mm jacks, terminal blocks, 2.54 mm pin headers,
    Faston tabs and Amass XT30 / XT60 / XT90 power connectors (right-angle and
    vertical, plated mounting tabs, 3D housing from the spec sheets);
  - transistors in TO-92 (oval pads, as KiCad's TO-92_Inline), TO-18, TO-126,
    TO-220, TO-247, TO-3P and TO-264 with each part's own pin order (pinouts
    that differ between makers are flagged); TO-3 power transistors get three
    wire pads, as the can sits on the chassis heatsink;
  - pots (9, 16 and 24 mm) and a 3296W trimmer;
  - real tube sockets (B9A noval, B7G, Magnoval, octal, UX4 with its pins on a
    16.25 mm circle, as real UX4 sockets), drawn from the
    component side; both sections of a dual tube share one socket, each on
    its own pins; a valve with its anode on a top cap gets a "cap" pad for
    the lead to it, and the suppressor grid joins the cathode (a
    triode-connected pentode's screen its anode); valves on bases with no
    board socket here (wire-lead subminiatures, nuvistors, 211, 845, ГМ-70,
    ГУ-50, 6С33С) go on wire pads to a chassis socket;
  - GoodComponent's real sockets (88 of them, for every base the tube library
    uses): pick one in the tube's *Tube socket* field (a dual valve's sections
    share it). The 21 PCB-mount ones with a
    published drawing get their own footprint (tails on the drawing's circle,
    flange screw holes, outline) and 3D model (body, flange, shield); a
    chassis or panel socket puts the valve on wire pads. The BOM lists the
    socket's item number with a link to its shop page; Soviet sockets too (29
    from tec.org.ru: ПЛК9-2П, ПЛК7-1П and ПЛК8-ПО with footprints and 3D from
    the shop's drawings, the rest chassis-mount);
  - board-mount EI transformers and chokes (EI30 to EI96, primary on one
    side, secondary on the other), with pins named as in the schematic;
  - toggle switches (SPDT, DPDT for a two-section switch), screw terminals
    (5.08 mm, 7.5 mm for mains), RCA, 3.5 mm and 6.35 mm jacks;
  - op-amps and the NE555 in DIP-8 and DIP-14; the amplifiers of a dual or
    quad (DA1.1 … DA1.4) share one package, each on its maker's pins;
  - JFETs in TO-92, regulators in TO-220 or TO-92 and the TL431 in TO-92,
    each with its maker's pin order.

  Dimensions are typical: check them against the part you buy. Parts that
  live on the chassis (transformers, chokes, speaker, pots) can instead get
  wire pads or a screw terminal.
  Every part's footprint can be changed in the inspector.
- **Standing resistors.** An axial resistor can stand up: *Mounting*
  (Horizontal | Vertical) in the inspector, or Shift+V. The lead spacing
  (max(D + d + 2R, the least the pads allow)), the silkscreen (a circle round
  pad 1, a pin 1 notch, the hairpin lead), a courtyard that grows with the
  height for a 5° lean and the height L + R + 2d all come from the body and
  lead sizes; the track ends on its pads follow. Set an enclosure height in
  Design rules and the check reports a part taller than it; the 3D view and
  STEP show the folded lead.
- **SMD versions.** Tick *SMD* in the inspector to switch a part to its
  surface-mount footprint, or a whole selection at once (each part that has
  one):
  - resistors 0603–2512 chips by power, capacitors 0603–2220 chips by value,
    electrolytics V-chip cans up to Ø18 mm;
  - signal diodes SOD-123, SOD-323 or MiniMELF, rectifiers and zeners SMA,
    SMB or SMC, LEDs 0805 or 1206;
  - small transistors SOT-23 (or SOT-89), TO-126 parts SOT-223 or DPAK,
    TO-220 parts D²PAK or DPAK; the NE555 and op-amps SOIC-8 or SOIC-14; a
    trimmer TC33; JFETs SOT-23 (D-S-G); regulators SOT-223, DPAK, D²PAK or
    SOT-89 (the tab on the pin the maker puts there); the TL431 SOT-23 or
    SOT-89.

  Valves, transformers, panel pots, jacks and big power transistors stay
  through-hole (the checkbox is greyed for them). SMD pads sit on the copper
  of the part's side only, with no hole: the ratsnest, the rule check, pours,
  Auto-route and manual routing all follow that (a track ending on an SMD pad
  on the other side asks for a via first). The 3D view, the part preview and
  STEP show the SMD bodies.
- **Placement.** New parts wait in a row below the board. Drag them on, or
  *Place all on the board*: each part goes where it sits in the schematic
  (the schematic's extent mapped onto the board), big parts first, each in the
  free spot nearest its place, electrolytics 10 mm from hot parts, so the
  signal runs across the board as across the sheet; then the parts spread
  into the room the board has, held near those places. Output and power
  transformers and filter chokes get wire pads by default (chassis-mounted). <kbd>Space</kbd> rotates,
  <kbd>M</kbd> moves a part to the bottom side. When the schematic changes, a
  banner offers the update; placed parts keep their spot.
- **Routing.** <kbd>X</kbd>: click a pad, click the corners (45° bends), end on
  a pad of the same net. <kbd>V</kbd> changes layer with a via. The track width
  comes from the net's class. The ratsnest shows what is still to route.
  The route goes on from its own vias; <kbd>Esc</kbd> right after <kbd>V</kbd>
  removes the via unless it already joins copper on the new layer.
  - While routing, a halo shows the clearance the net's class needs. It turns
    red, and the click is refused, when the next segment would come too close
    to another net's copper or a mounting hole (<kbd>Shift</kbd>+click places
    it anyway).
  - **Push and shove** (*Route ▾ → Push and shove*, <kbd>Shift</kbd>+<kbd>X</kbd>,
    on by default): other nets' tracks in the way step aside by just the
    clearance they lack, with 45° jogs, and push the next ones in turn. Pads,
    vias, holes, keep-outs, locked tracks and track ends stay put; if a push
    needs them to move, nothing moves and the status line says why.
    <kbd>Backspace</kbd> puts pushed tracks back.
  - A track entering a tube pin may pass the socket's other pins as closely as
    the pin itself does: the socket's own pin spacing is a limit no layout can
    beat.
- **Impedance, pairs, lengths.** *Board ▾ → Impedance calculator…*: Z₀ and
  Zdiff of a track or pair on each layer from the stack (εr and each
  dielectric's thickness in Board setup), or the width and gap for a target.
  *Design rules* gets differential pairs (width, gap, skew) and length groups
  (tolerance, target); the check reports skew and short nets, and a track's
  right-click menu routes a pair's partner alongside or adds a meander that
  makes up the missing length. The KiCad export writes them as custom rules.
- **Auto-route** routes the open connections with the board's own grid
  router, in the browser; no server is needed. Ticked in *Route ▾ →
  Freerouting…*, [Freerouting](https://www.freerouting.app) (free, GPL-3)
  routes first and the grid router finishes what it leaves. Freerouting runs
  on this site's server, your own computer, or another one on your network.
  - Start its API server with Java 25 and `freerouting.jar`:

    ```sh
    java -jar freerouting.jar --gui.enabled=false --api_server.enabled=true \
      --api_server.authentication.enabled=false \
      --api_server.cors_origins=https://aerocat.tech
    ```

    or with its Docker image (it then has to listen on all addresses):

    ```sh
    docker run -d --name freerouting --restart unless-stopped -p 37864:37864 \
      ghcr.io/freerouting/freerouting:latest java -jar /app/freerouting-executable.jar \
      --gui.enabled=false --api_server.enabled=true \
      --api_server.endpoints=http://0.0.0.0:37864 \
      --api_server.authentication.enabled=false \
      --api_server.cors_origins=https://aerocat.tech
    ```

    `cors_origins` must name the address the CAD is opened from (use your
    own when you run it locally); without it Freerouting answers but the
    browser keeps the page out. `authentication.enabled=false` turns off its
    API key.
  - Your own Freerouting answers at `http://127.0.0.1:37864` by default
    (until it answers, Auto-route uses the grid router alone). *Route ▾ → Freerouting…* sets another address
    (a PC or server on your network: its IP, and `:port` if not 37864), tests
    it, and shows both start commands ready to copy. When it does not answer,
    the dialog says why: Freerouting runs but was started without this page's
    address in `cors_origins`, something else answers there, it wants an API
    key, or nothing answers.
  - An https page calling a plain http address on another computer: Chrome,
    Vivaldi and other Chromium browsers ask once to allow access to the local
    network; allow it. If the browser refuses, an SSH tunnel makes it local:
    `ssh -N -L 37864:127.0.0.1:37864 user@that-pc`, then use the default
    address.
  - The board goes out with its design rules: each net's track width (its
    class, or its DC current) and the clearance between every two nets, by
    voltage too. Pour nets, and GND with star grounding, are left to the
    pour. A pad crowded by its footprint's neighbours first gets a short
    straight lead to where the full clearance holds.
  - Before routing it clears copper left from where the parts used to be:
    loose ends, copper reaching no pad or joining two nets, tracks breaking a
    clearance. Those connections are routed afresh; locked copper stays.
  - What it cannot route within the rules stays in the ratsnest, and one
    <kbd>Ctrl</kbd>+<kbd>Z</kbd> takes the whole run back. The Gubin board
    (07), routed from scratch, gets 46 of its 59 connections in about 7 s,
    with no rule violations.
  - By hand: *Export ▾ → Freerouting design (DSN)*, route it in
    Freerouting's window or `java -jar freerouting.jar -de board.dsn -do
    board.ses`, then *Route ▾ → Import routes (SES)…*.
- **Finish routing** (*Route ▾*; Route & nudge before 3.131), for when
  Auto-route can't fit everything and you want to keep your layout.
  It routes, then, while connections are left, moves the unlocked parts near
  them a little and routes again, for up to 5 rounds. A round that doesn't help
  is undone. The moves come from simulated annealing on wire length, ratsnest
  crossings, crowding (RUDY wire density) and how far parts go. Every move keeps
  the design rules: the outline, courtyards, mounting holes, keep-outs, the
  heat gap and clearance by voltage. Locked parts, valves, transformers,
  controls and connectors never move. Parts and tracks that wall in a pin
  (found by a max-flow escape check) move or come up too. The nets that
  failed are routed first in each round, and what Freerouting leaves is tried
  once more on a grid (Lee's maze search), kept only if it keeps every rule,
  then exactly: a small window round each leftover becomes a SAT problem
  (one connection per cell, clearances between nets) solved in the page,
  which may take up and relay the tracks walling it in.
  Last, it spreads the movable parts over the whole board (wire length
  against an electrostatic density of their area, shut-in parts counted
  bigger), puts each on the nearest legal grid place and routes afresh,
  keeping that only if it is better. The status line lists what moved, and
  <kbd>Ctrl</kbd>+<kbd>Z</kbd> takes the whole run back. On example 07 routed
  from scratch, it leaves 6 connections open.
- **Design from scratch** (*Route ▾*; Rearrange board before 3.131): an
  automatic layout. Every unlocked part except the panel ones comes off and
  goes back, valves and transformers too. Nine layouts are made in a
  background worker: from the schematic's places, spread over the board
  (valves and high-voltage parts counted bigger), with each part's quarter turn
  chosen as it goes for the shortest wiring and fewest net crossings (as the
  Cypress PCB placer does), then polished by annealing. Each is scored
  without routing (shut-in pins, ratsnest crossings with high-voltage nets
  counted triple, ratsnest length); the best of each kind, three in all, are
  routed, the best routed one stays (the old layout included), and Finish
  routing's rounds work on what is left. The outline, holes, keep-outs,
  locked parts and locked copper hold throughout. A progress bar in the status
  line shows the step and the time so far.
- **Stitching vias**: a GND pad the pour cannot reach (shut in by other
  copper or a high-voltage pin's clearance) gets a short track on the other
  layer and a via down into the pour, tried nearest first and kept only if it
  joins without a new rule violation. Routing does this by itself.
- **Tidy tracks** is automatic: after each Auto-route, Finish routing and
  Design from scratch pass the unlocked tracks are pulled tight (grid-finisher
  staircases and detours become straight and 45° runs wherever every clearance
  still holds).
- **Unroute** (*Route ▾*) removes every track and via, to route again
  from scratch. Locked tracks and vias stay; <kbd>Ctrl</kbd>+<kbd>Z</kbd>
  brings them all back.
- **Several at once:** drag a box over empty space to select what lies inside
  it (left to right) or what it touches (right to left); <kbd>Shift</kbd>+click
  adds or removes single things. Drag any selected item and everything
  selected moves. <kbd>Space</kbd> turns the group 90° about its middle, the
  arrows nudge it one grid step (<kbd>Shift</kbd>: ten). The inspector aligns
  the selected parts (left, centre, right, top, middle, bottom) or spreads
  them evenly.
- **Locking:** <kbd>L</kbd> locks the selection (parts, tracks, vias, texts,
  holes, pours, keep-outs). Locked things cannot be dragged, nudged, turned or
  deleted, and show a padlock. The mounting holes from Board setup come
  locked.
- **Keep-out areas** (*Keep-out*, <kbd>K</kbd>): on either or both copper
  layers, forbidding tracks, vias, copper pour and, if you choose, parts. Use
  them under a power transformer, round the mains entry or along heater
  wiring. Routing refuses to enter them, pours leave them empty, and the check
  reports anything inside.
- **Editing tracks:** drag a segment sideways and its neighbours follow (a 45°
  corner stays 45°; a track's end gets a jog). <kbd>U</kbd> selects the whole
  connected track, so <kbd>Del</kbd> removes it or the inspector sets its
  width. <kbd>Shift</kbd>+click adds tracks to the selection. Deleting one
  track of a route takes the copper of that route it leaves hanging (stubs
  and vias touching nothing) with it, up to the pads, a pour or copper still
  in use; locked copper stays.
- **Copper pours** (*Pour*, or *+ GND plane* / *+ GND pour round the parts* in
  the board inspector, or *+ GND pour round these parts* for a selection):
  - click its outline or its copper to select it (Del deletes it); it is a
    shape you edit: drag a corner, drag the **+** in the middle of
    an edge to add a corner, double-click a corner to remove it, drag its
    outline or inside it to move it; the copper refills as you drag. Its
    inspector reshapes it round the parts or over the whole board, and the
    board outline (round corners too) cuts it;
  - the pour keeps each other net's clearance (by its class and by voltage),
    the edge clearance and the mounting holes clear, so it shorts nothing;
  - its net's pads join through thermal reliefs (or solidly), its tracks and
    vias solidly; a via dropped in a pour takes its net (stitching);
  - pieces that reach nothing (islands) are removed, and the ratsnest counts
    only what the pour really joins.
- **Nets** tab: every net with its class, its DC current, what is left to
  route, and its track length. Click a net (or point and press <kbd>`</kbd>) to highlight it and dim
  everything else.
- **Cross-probing:** a part picked on the board is selected in the schematic,
  and a part selected in the schematic is selected (and shown) on the board.
  A net highlighted on the board selects its wires in the schematic, and wires
  of one net selected in the schematic light that net up on the board.
- **Comfort:** a card at the pointer for pads, parts, tracks and vias (net,
  class, voltage, current) and, while routing, for the route (net, width,
  layer, length); <kbd>W</kbd> steps the width while routing; a right-click
  menu for what is under the pointer; <kbd>+</kbd> / <kbd>−</kbd>, a zoom bar
  and <kbd>Z</kbd> (zoom to the selection); <kbd>Ctrl</kbd>+<kbd>F</kbd> finds
  a part or net; <kbd>\\</kbd> hides the side panels; the checks and layers
  fold away; values never cover references.
- **Mounting holes** are not plated (NPTH) or plated (PTH): a plated one has a
  copper ring on both sides (Ø 6 mm round an M3 hole by default) and may
  take a net, GND for a grounded chassis screw, which a pour of that net joins.
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
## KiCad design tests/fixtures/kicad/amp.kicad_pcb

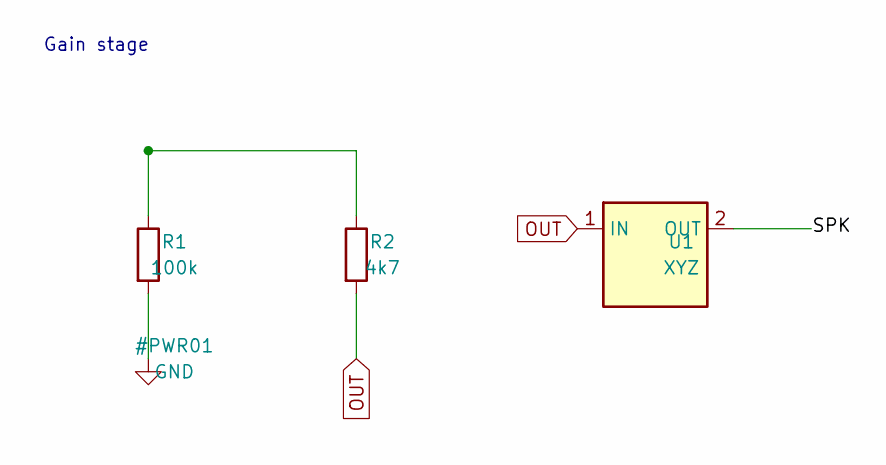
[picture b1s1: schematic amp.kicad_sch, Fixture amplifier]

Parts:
R1: 100k; R_Axial_P10.16
R2: 4k7; R_Axial_P10.16
U1: XYZ; XYZ_SMD

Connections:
/OUT: R2.2, U1.1 (IN)
/SPK: U1.2 (OUT)
GND: R1.2
unnamed: R1.1, R2.1

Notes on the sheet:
Gain stage

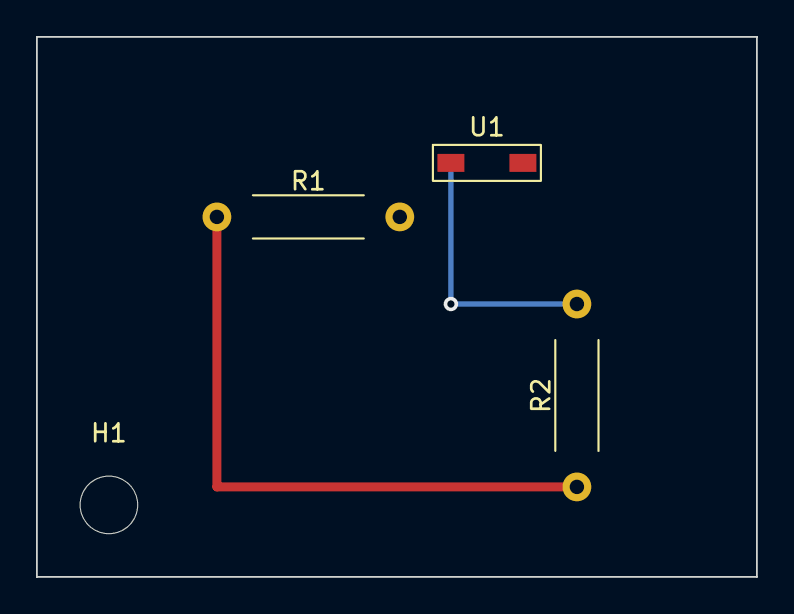
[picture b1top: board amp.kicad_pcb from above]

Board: 2 copper layers, 40.0 x 30.0 mm, 4 parts (0 on the bottom side), 2 nets.

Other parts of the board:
H1: MountingHole_3.2mm_M3

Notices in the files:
README.md:
License:
[MIT](LICENSE)
Credits for the models, data, software, example circuits and services the app
uses are in Help → *About & credits* and the manual's last section (`about.js`).
